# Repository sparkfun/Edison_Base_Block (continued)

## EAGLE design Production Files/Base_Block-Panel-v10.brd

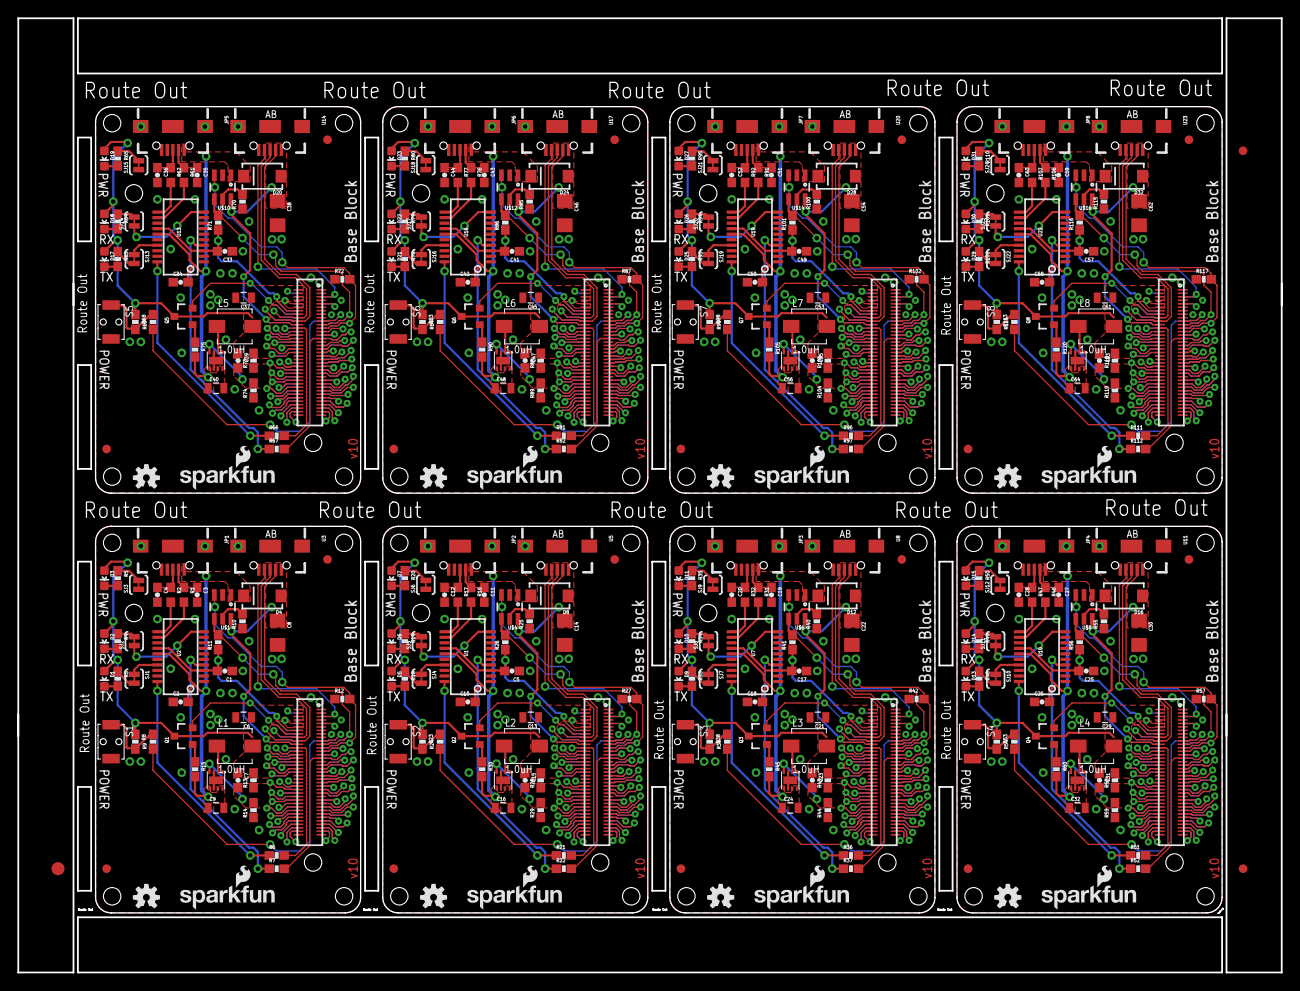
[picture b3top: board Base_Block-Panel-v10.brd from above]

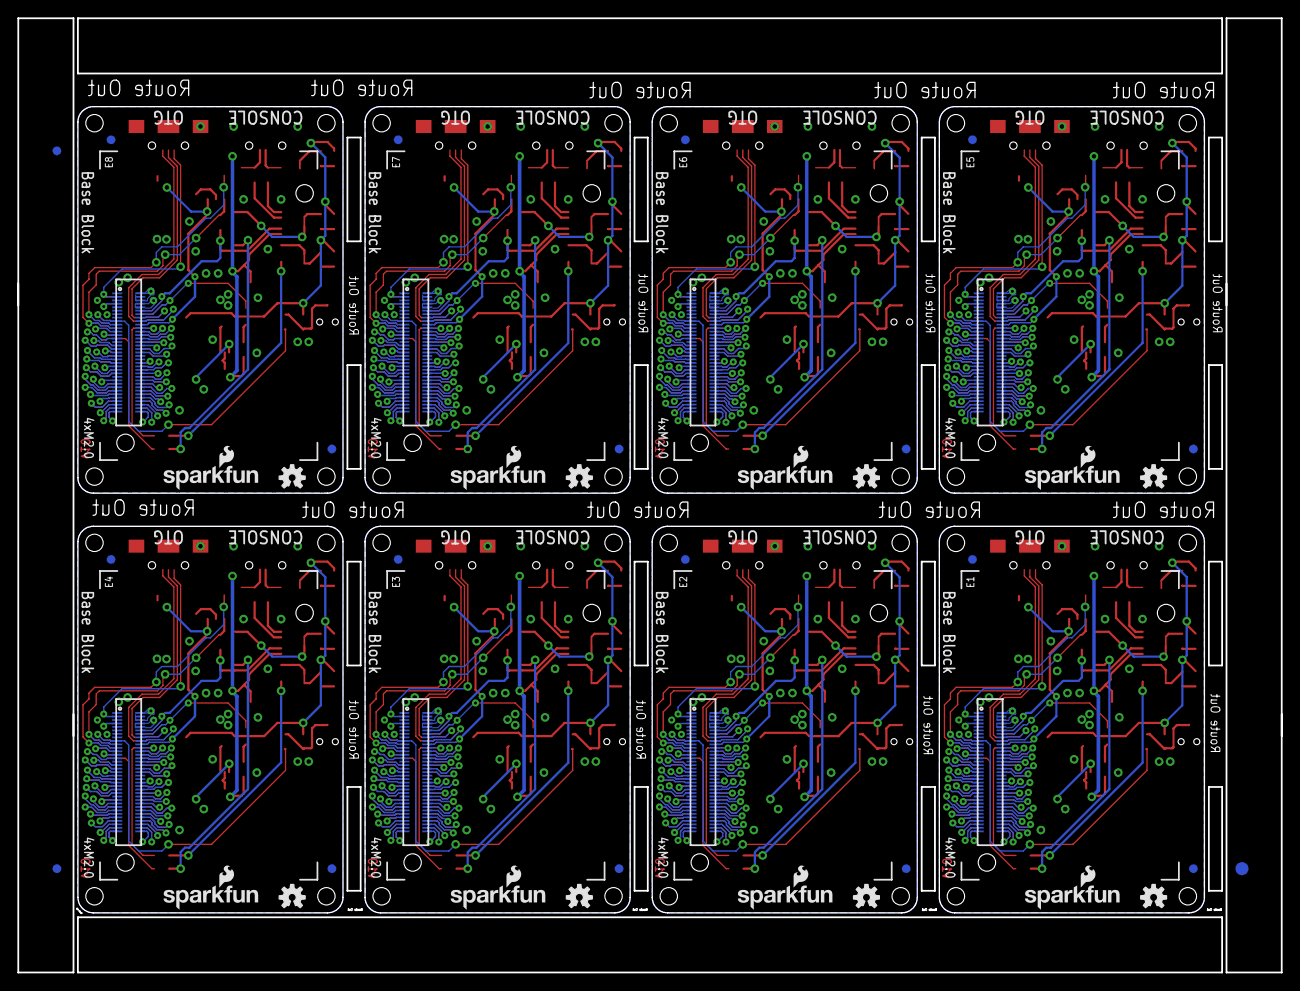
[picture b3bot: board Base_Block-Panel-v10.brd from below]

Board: 2 copper layers, 145.3 x 109.7 mm, 390 parts (51 on the bottom side), 624 nets.

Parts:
C1, C2, C5, C10, C17, C18, C25, C26, C33, C34, C41, C42, C49, C50, C57, C58: 0.1uF; 0603-CAP
C3, C4, C7, C11, C12, C15, C19, C20, C23, C27, C28, C31, C35, C36, C39, C43, C44, C47, C51, C52, C55, C59, C60, C63: 47pF; 0603-CAP
C6, C9, C13, C16, C21, C24, C29, C32, C37, C40, C45, C48, C53, C56, C61, C64: 22uF; 0805
C8, C14, C22, C30, C38, C46, C54, C62: 10uF; 1206
D1, D5, D9, D13, D17, D21, D25, D29: RED; LED-0603
D2, D6, D10, D14, D18, D22, D26, D30: YELLOW; LED-0603
D3, D7, D11, D15, D19, D23, D27, D31: BLUE; LED-0603
D4, D8, D12, D16, D20, D24, D28, D32: SMA-DIODE
E1, E2, E3, E4, E5, E6, E7, E8: EDISON_CONNECTOR_FULLMOUNTING_HOLES; EDISON_DAUGHTER
E$1, E$2: FIDUCIAL-1.5X3
E$3, E$4, E$5, E$6: FIDUCIAL-1X2
FID1, FID2, FID3, FID4, FID5, FID6, FID7, FID8, FID9, FID10, FID11, FID12, FID13, FID14, FID15, FID16, FID17, FID18, FID19, FID20, FID21, FID22, FID23, FID24, FID25, FID26, FID27, FID28, FID29, FID30, FID31, FID32: FIDUCIAL1X2; FIDUCIAL-1X2
JP1, JP2, JP3, JP4, JP5, JP6, JP7, JP8: USB_MICROB; USB-B-MICRO-SMD_V03
L1, L2, L3, L4, L5, L6, L7, L8: 1.0uH; INDUCTOR-SRP4020
LOGO1, LOGO3, LOGO6, LOGO7, LOGO10, LOGO11, LOGO14, LOGO15, LOGO18, LOGO19, LOGO22, LOGO23, LOGO26, LOGO27, LOGO30, LOGO31: SFE_LOGO_NAME_FLAME.1_INCH; SFE_LOGO_NAME_FLAME_.1
LOGO2, LOGO4, LOGO5, LOGO8, LOGO9, LOGO12, LOGO13, LOGO16, LOGO17, LOGO20, LOGO21, LOGO24, LOGO25, LOGO28, LOGO29, LOGO32: OSHW-LOGOS; OSHW-LOGO-S
Q1, Q2, Q3, Q4, Q5, Q6, Q7, Q8: BSS138; SOT23-3
R1, R2, R16, R17, R31, R32, R46, R47, R61, R62, R76, R77, R91, R92, R106, R107: 27; 0603
R3, R4, R5, R15, R18, R19, R20, R30, R33, R34, R35, R45, R48, R49, R50, R60, R63, R64, R65, R75, R78, R79, R80, R90, R93, R94, R95, R105, R108, R109, R110, R120: 1K; 0603-RES
R6, R7, R21, R22, R36, R37, R51, R52, R66, R67, R81, R82, R96, R97, R111, R112: 100; 0603-RES
R8, R11, R23, R26, R38, R41, R53, R56, R68, R71, R83, R86, R98, R101, R113, R116: 10K; 0603-RES
R9, R24, R39, R54, R69, R84, R99, R114: 220; 0603-RES
R10, R25, R40, R55, R70, R85, R100, R115: 287; 0603-RES
R12, R27, R42, R57, R72, R87, R102, R117: 100k; 0603-RES
R13, R28, R43, R58, R73, R88, R103, R118: 680k; 0603-RES
R14, R29, R44, R59, R74, R89, R104, R119: 120k; 0603-RES
S1, S2, S3, S4, S5, S6, S7, S8: POWER; TACTILE_SWITCH-SMD-RIGHT-ANGLE
SJ1, SJ2, SJ3, SJ4, SJ5, SJ6, SJ7, SJ8, SJ9, SJ10, SJ11, SJ12, SJ13, SJ14, SJ15, SJ16, SJ17, SJ18, SJ19, SJ20, SJ21, SJ22, SJ23, SJ24: JUMPER-PAD-2-NC_BY_TRACE; PAD-JUMPER-2-NC_BY_TRACE_YES_SILK
U1, U2, U7, U10, U13, U16, U19, U22: FTS31XS-U; SSOP20_L
U3, U5, U8, U11, U14, U17, U20, U23: USB-AB-MICRO-SMD_V03
U4, U6, U9, U12, U15, U18, U21, U24: TPS62065; WSON-8-PAD
U$1, U$4, U$6, U$8, U$10, U$12, U$14, U$16: MIC2039; SOT23-6
U$2, U$3, U$5, U$7, U$9, U$11, U$13, U$15: EDISON_CONNECTOR_FULLHEADER; DF40C-70DP-0.4(51)

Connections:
1.8V: C1.2, E1.12, R11.1, U2.3, U2.14, U$3.12
1.8V1: C5.2, E2.12, R26.1, U1.3, U1.14, U$2.12
1.8V2: C17.2, E3.12, R41.1, U7.3, U7.14, U$5.12
1.8V3: C25.2, E4.12, R56.1, U10.3, U10.14, U$7.12
1.8V4: C33.2, E5.12, R71.1, U13.3, U13.14, U$9.12
1.8V5: C41.2, E6.12, R86.1, U16.3, U16.14, U$11.12
1.8V6: C49.2, E7.12, R101.1, U19.3, U19.14, U$13.12
1.8V7: C57.2, E8.12, R116.1, U22.3, U22.14, U$15.12
3.3V: E1.8, E1.10, U$3.8, U$3.10
3.3V1: E2.8, E2.10, U$2.8, U$2.10
3.3V2: E3.8, E3.10, U$5.8, U$5.10
3.3V3: E4.8, E4.10, U$7.8, U$7.10
3.3V4: E5.8, E5.10, U$9.8, U$9.10
3.3V5: E6.8, E6.10, U$11.8, U$11.10
3.3V6: E7.8, E7.10, U$13.8, U$13.10
3.3V7: E8.8, E8.10, U$15.8, U$15.10
5V: C2.2, C9.1, D4.C, JP1.VBUS1, R15.2, U2.15, U4.5, U4.7, U4.8, U$1.1
5V1: C10.2, C16.1, D8.C, JP2.VBUS1, R30.2, U1.15, U6.5, U6.7, U6.8, U$4.1
5V2: C18.2, C24.1, D12.C, JP3.VBUS1, R45.2, U7.15, U9.5, U9.7, U9.8, U$6.1
5V3: C26.2, C32.1, D16.C, JP4.VBUS1, R60.2, U10.15, U12.5, U12.7, U12.8, U$8.1
5V4: C34.2, C40.1, D20.C, JP5.VBUS1, R75.2, U13.15, U15.5, U15.7, U15.8, U$10.1
5V5: C42.2, C48.1, D24.C, JP6.VBUS1, R90.2, U16.15, U18.5, U18.7, U18.8, U$12.1
5V6: C50.2, C56.1, D28.C, JP7.VBUS1, R105.2, U19.15, U21.5, U21.7, U21.8, U$14.1
5V7: C58.2, C64.1, D32.C, JP8.VBUS1, R120.2, U22.15, U24.5, U24.7, U24.8, U$16.1
DCIN: E1.14, Q1.2, U$3.14
DCIN1: E2.14, Q2.2, U$2.14
DCIN2: E3.14, Q3.2, U$5.14
DCIN3: E4.14, Q4.2, U$7.14
DCIN4: E5.14, Q5.2, U$9.14
DCIN5: E6.14, Q6.2, U$11.14
DCIN6: E7.14, Q7.2, U$13.14
DCIN7: E8.14, Q8.2, U$15.14
FAULT: E1.19, R11.2, U$1.4, U$3.19
FAULT1: E2.19, R26.2, U$2.19, U$4.4
FAULT2: E3.19, R41.2, U$5.19, U$6.4
FAULT3: E4.19, R56.2, U$7.19, U$8.4
FAULT4: E5.19, R71.2, U$9.19, U$10.4
FAULT5: E6.19, R86.2, U$11.19, U$12.4
FAULT6: E7.19, R101.2, U$13.19, U$14.4
FAULT7: E8.19, R116.2, U$15.19, U$16.4
FW_RCVR: E1.69, U$3.69
FW_RCVR1: E2.69, U$2.69
FW_RCVR2: E3.69, U$5.69
FW_RCVR3: E4.69, U$7.69
FW_RCVR4: E5.69, U$9.69
FW_RCVR5: E6.69, U$11.69
FW_RCVR6: E7.69, U$13.69
FW_RCVR7: E8.69, U$15.69
GND: C1.1, C2.1, C3.2, C4.2, C6.2, C8.2, C9.2, E1.1, E1.5, E1.9, E1.11, E1.13, E1.15, JP1.GND1, JP1.SHIELD1, JP1.SHIELD2, JP1.SHIELD3, R10.1, R12.1, R14.1, S1.2, SJ3.1, U2.6, U2.16, U3.GND1, U4.1, U4.3, U4.6, U4.PAD, U$1.2, U$3.1, U$3.5, U$3.9, U$3.11, U$3.13, U$3.15
GND1: C5.1, C10.1, C11.2, C12.2, C13.2, C14.2, C16.2, E2.1, E2.5, E2.9, E2.11, E2.13, E2.15, JP2.GND1, JP2.SHIELD1, JP2.SHIELD2, JP2.SHIELD3, R25.1, R27.1, R29.1, S2.2, SJ6.1, U1.6, U1.16, U5.GND1, U6.1, U6.3, U6.6, U6.PAD, U$2.1, U$2.5, U$2.9, U$2.11, U$2.13, U$2.15, U$4.2
GND2: C17.1, C18.1, C19.2, C20.2, C21.2, C22.2, C24.2, E3.1, E3.5, E3.9, E3.11, E3.13, E3.15, JP3.GND1, JP3.SHIELD1, JP3.SHIELD2, JP3.SHIELD3, R40.1, R42.1, R44.1, S3.2, SJ9.1, U7.6, U7.16, U8.GND1, U9.1, U9.3, U9.6, U9.PAD, U$5.1, U$5.5, U$5.9, U$5.11, U$5.13, U$5.15, U$6.2
GND3: C25.1, C26.1, C27.2, C28.2, C29.2, C30.2, C32.2, E4.1, E4.5, E4.9, E4.11, E4.13, E4.15, JP4.GND1, JP4.SHIELD1, JP4.SHIELD2, JP4.SHIELD3, R55.1, R57.1, R59.1, S4.2, SJ12.1, U10.6, U10.16, U11.GND1, U12.1, U12.3, U12.6, U12.PAD, U$7.1, U$7.5, U$7.9, U$7.11, U$7.13, U$7.15, U$8.2
GND4: C33.1, C34.1, C35.2, C36.2, C37.2, C38.2, C40.2, E5.1, E5.5, E5.9, E5.11, E5.13, E5.15, JP5.GND1, JP5.SHIELD1, JP5.SHIELD2, JP5.SHIELD3, R70.1, R72.1, R74.1, S5.2, SJ15.1, U13.6, U13.16, U14.GND1, U15.1, U15.3, U15.6, U15.PAD, U$9.1, U$9.5, U$9.9, U$9.11, U$9.13, U$9.15, U$10.2
GND5: C41.1, C42.1, C43.2, C44.2, C45.2, C46.2, C48.2, E6.1, E6.5, E6.9, E6.11, E6.13, E6.15, JP6.GND1, JP6.SHIELD1, JP6.SHIELD2, JP6.SHIELD3, R85.1, R87.1, R89.1, S6.2, SJ18.1, U16.6, U16.16, U17.GND1, U18.1, U18.3, U18.6, U18.PAD, U$11.1, U$11.5, U$11.9, U$11.11, U$11.13, U$11.15, U$12.2
GND6: C49.1, C50.1, C51.2, C52.2, C53.2, C54.2, C56.2, E7.1, E7.5, E7.9, E7.11, E7.13, E7.15, JP7.GND1, JP7.SHIELD1, JP7.SHIELD2, JP7.SHIELD3, R100.1, R102.1, R104.1, S7.2, SJ21.1, U19.6, U19.16, U20.GND1, U21.1, U21.3, U21.6, U21.PAD, U$13.1, U$13.5, U$13.9, U$13.11, U$13.13, U$13.15, U$14.2
GND7: C57.1, C58.1, C59.2, C60.2, C61.2, C62.2, C64.2, E8.1, E8.5, E8.9, E8.11, E8.13, E8.15, JP8.GND1, JP8.SHIELD1, JP8.SHIELD2, JP8.SHIELD3, R115.1, R117.1, R119.1, S8.2, SJ24.1, U22.6, U22.16, U23.GND1, U24.1, U24.3, U24.6, U24.PAD, U$15.1, U$15.5, U$15.9, U$15.11, U$15.13, U$15.15, U$16.2
GP1: E2.48, U$2.48
GP2: E2.42, U$2.42
GP3: E2.34, U$2.34
GP4: E2.32, U$2.32
GP5: E2.30, U$2.30
GP6: E2.28, U$2.28
GP7: E2.26, U$2.26
GP8: E2.25, U$2.25
GP9: E2.24, U$2.24
GP10: E3.48, U$5.48
GP11: E3.42, U$5.42
GP12: E3.34, U$5.34
GP12_PWM0: E1.35, U$3.35
GP12_PWM1: E2.35, U$2.35
GP12_PWM2: E3.35, U$5.35
GP12_PWM3: E4.35, U$7.35
GP12_PWM4: E5.35, U$9.35
GP12_PWM5: E6.35, U$11.35
GP12_PWM6: E7.35, U$13.35
GP12_PWM7: E8.35, U$15.35
GP13: E3.32, U$5.32
GP13_PWM1: E1.33, U$3.33
GP13_PWM2: E2.33, U$2.33
GP13_PWM3: E3.33, U$5.33
GP13_PWM4: E4.33, U$7.33
GP13_PWM5: E5.33, U$9.33
GP13_PWM6: E6.33, U$11.33
GP13_PWM7: E7.33, U$13.33
GP13_PWM8: E8.33, U$15.33
GP14: E1.48, U$3.48
GP15: E1.42, U$3.42
GP16: E3.30, U$5.30
GP17: E3.28, U$5.28
GP18: E3.26, U$5.26
GP19: E3.25, U$5.25
GP19_I2C_1_SCL: E1.41, U$3.41
GP19_I2C_1_SCL1: E2.41, U$2.41
GP19_I2C_1_SCL2: E3.41, U$5.41
GP19_I2C_1_SCL3: E4.41, U$7.41
GP19_I2C_1_SCL4: E5.41, U$9.41
GP19_I2C_1_SCL5: E6.41, U$11.41
GP19_I2C_1_SCL6: E7.41, U$13.41
GP19_I2C_1_SCL7: E8.41, U$15.41
GP20: E3.24, U$5.24
GP20_I2C_1_SDA: E1.43, U$3.43
GP20_I2C_1_SDA1: E2.43, U$2.43
GP20_I2C_1_SDA2: E3.43, U$5.43
GP20_I2C_1_SDA3: E4.43, U$7.43
GP20_I2C_1_SDA4: E5.43, U$9.43
GP20_I2C_1_SDA5: E6.43, U$11.43
GP20_I2C_1_SDA6: E7.43, U$13.43
GP20_I2C_1_SDA7: E8.43, U$15.43
GP21: E4.48, U$7.48
GP22: E4.42, U$7.42
GP23: E4.34, U$7.34
GP24: E4.32, U$7.32
GP25: E4.30, U$7.30
GP26: E4.28, U$7.28
GP27: E4.26, U$7.26
GP27_I2C_6_SCL: E1.45, U$3.45
GP27_I2C_6_SCL1: E2.45, U$2.45
GP27_I2C_6_SCL2: E3.45, U$5.45
GP27_I2C_6_SCL3: E4.45, U$7.45
GP27_I2C_6_SCL4: E5.45, U$9.45
GP27_I2C_6_SCL5: E6.45, U$11.45
GP27_I2C_6_SCL6: E7.45, U$13.45
GP27_I2C_6_SCL7: E8.45, U$15.45
GP28: E4.25, U$7.25
GP28_I2C_6_SDA: E1.47, U$3.47
GP28_I2C_6_SDA1: E2.47, U$2.47
GP28_I2C_6_SDA2: E3.47, U$5.47
GP28_I2C_6_SDA3: E4.47, U$7.47
GP28_I2C_6_SDA4: E5.47, U$9.47
GP28_I2C_6_SDA5: E6.47, U$11.47
GP28_I2C_6_SDA6: E7.47, U$13.47
GP28_I2C_6_SDA7: E8.47, U$15.47
GP29: E4.24, U$7.24
GP30: E5.48, U$9.48
GP31: E5.42, U$9.42
GP32: E5.34, U$9.34
GP33: E5.32, U$9.32
GP34: E5.30, U$9.30
GP35: E5.28, U$9.28
GP36: E5.26, U$9.26
GP37: E5.25, U$9.25
GP38: E5.24, U$9.24
GP39: E6.48, U$11.48
GP40: E6.42, U$11.42
GP40_I2S_2_CLK: E1.52, U$3.52
GP40_I2S_2_CLK1: E2.52, U$2.52
GP40_I2S_2_CLK2: E3.52, U$5.52
GP40_I2S_2_CLK3: E4.52, U$7.52
GP40_I2S_2_CLK4: E5.52, U$9.52
GP40_I2S_2_CLK5: E6.52, U$11.52
GP40_I2S_2_CLK6: E7.52, U$13.52
GP40_I2S_2_CLK7: E8.52, U$15.52
GP41: E6.34, U$11.34
GP41_I2S_2_FS: E1.54, U$3.54
GP41_I2S_2_FS1: E2.54, U$2.54
GP41_I2S_2_FS2: E3.54, U$5.54
GP41_I2S_2_FS3: E4.54, U$7.54
GP41_I2S_2_FS4: E5.54, U$9.54
GP41_I2S_2_FS5: E6.54, U$11.54
GP41_I2S_2_FS6: E7.54, U$13.54
GP41_I2S_2_FS7: E8.54, U$15.54
GP42: E6.32, U$11.32
GP42_I2S_2_RXD: E1.50, U$3.50
GP42_I2S_2_RXD1: E2.50, U$2.50
GP42_I2S_2_RXD2: E3.50, U$5.50
GP42_I2S_2_RXD3: E4.50, U$7.50
GP42_I2S_2_RXD4: E5.50, U$9.50
GP42_I2S_2_RXD5: E6.50, U$11.50
GP42_I2S_2_RXD6: E7.50, U$13.50
GP42_I2S_2_RXD7: E8.50, U$15.50
GP43: E6.30, U$11.30
GP43_I2S_2_TXD: E1.56, U$3.56
GP43_I2S_2_TXD1: E2.56, U$2.56
GP43_I2S_2_TXD2: E3.56, U$5.56
GP43_I2S_2_TXD3: E4.56, U$7.56
GP43_I2S_2_TXD4: E5.56, U$9.56
GP43_I2S_2_TXD5: E6.56, U$11.56
GP43_I2S_2_TXD6: E7.56, U$13.56
GP43_I2S_2_TXD7: E8.56, U$15.56
GP44: E1.24, U$3.24
GP45: E1.26, U$3.26
GP46: E1.28, U$3.28
GP47: E1.30, U$3.30
GP48: E1.32, U$3.32
GP49: E1.34, U$3.34
GP50: E6.28, U$11.28
GP51: E6.26, U$11.26
GP52: E6.25, U$11.25
GP53: E6.24, U$11.24
GP54: E7.48, U$13.48
GP55: E7.42, U$13.42
GP56: E7.34, U$13.34
GP57: E7.32, U$13.32
GP58: E7.30, U$13.30
GP59: E7.28, U$13.28
GP60: E7.26, U$13.26
GP61: E7.25, U$13.25
GP62: E7.24, U$13.24
GP63: E8.48, U$15.48
GP64: E8.42, U$15.42
GP65: E8.34, U$15.34
GP66: E8.32, U$15.32
GP67: E8.30, U$15.30
GP68: E8.28, U$15.28
GP69: E8.26, U$15.26
GP70: E8.25, U$15.25
GP71: E8.24, U$15.24
GP77_SD_0_CD#: E1.60, U$3.60
GP77_SD_0_CD#1: E2.60, U$2.60
GP77_SD_0_CD#2: E3.60, U$5.60
GP77_SD_0_CD#3: E4.60, U$7.60
GP77_SD_0_CD#4: E5.60, U$9.60
GP77_SD_0_CD#5: E6.60, U$11.60
GP77_SD_0_CD#6: E7.60, U$13.60
GP77_SD_0_CD#7: E8.60, U$15.60
GP78_SD_0_CLK: E1.58, U$3.58
GP78_SD_0_CLK1: E2.58, U$2.58
GP78_SD_0_CLK2: E3.58, U$5.58
GP78_SD_0_CLK3: E4.58, U$7.58
GP78_SD_0_CLK4: E5.58, U$9.58
GP78_SD_0_CLK5: E6.58, U$11.58
GP78_SD_0_CLK6: E7.58, U$13.58
GP78_SD_0_CLK7: E8.58, U$15.58
GP79_SD_0_CMD: E1.62, U$3.62
GP79_SD_0_CMD1: E2.62, U$2.62
GP79_SD_0_CMD2: E3.62, U$5.62
GP79_SD_0_CMD3: E4.62, U$7.62
GP79_SD_0_CMD4: E5.62, U$9.62
GP79_SD_0_CMD5: E6.62, U$11.62
GP79_SD_0_CMD6: E7.62, U$13.62
GP79_SD_0_CMD7: E8.62, U$15.62
GP80_SD_0_DAT0: E1.66, U$3.66
GP80_SD_0_DAT1: E2.66, U$2.66
GP80_SD_0_DAT2: E3.66, U$5.66
GP80_SD_0_DAT3: E4.66, U$7.66
GP80_SD_0_DAT4: E5.66, U$9.66
GP80_SD_0_DAT5: E6.66, U$11.66
GP80_SD_0_DAT6: E7.66, U$13.66
GP80_SD_0_DAT7: E8.66, U$15.66
GP81_SD_0_DAT1: E1.70, U$3.70
GP81_SD_0_DAT2: E2.70, U$2.70
GP81_SD_0_DAT3: E3.70, U$5.70
GP81_SD_0_DAT4: E4.70, U$7.70
GP81_SD_0_DAT5: E5.70, U$9.70
GP81_SD_0_DAT6: E6.70, U$11.70
GP81_SD_0_DAT7: E7.70, U$13.70
GP81_SD_0_DAT8: E8.70, U$15.70
GP82_SD_0_DAT1: E2.64, U$2.64
GP82_SD_0_DAT2: E1.64, U$3.64
GP82_SD_0_DAT3: E3.64, U$5.64
GP82_SD_0_DAT4: E4.64, U$7.64
GP82_SD_0_DAT5: E5.64, U$9.64
GP82_SD_0_DAT6: E6.64, U$11.64
GP82_SD_0_DAT7: E7.64, U$13.64
GP82_SD_0_DAT8: E8.64, U$15.64
GP83_SD_0_DAT1: E2.68, U$2.68
GP83_SD_0_DAT2: E3.68, U$5.68
GP83_SD_0_DAT3: E1.68, U$3.68
GP83_SD_0_DAT4: E4.68, U$7.68
GP83_SD_0_DAT5: E5.68, U$9.68
GP83_SD_0_DAT6: E6.68, U$11.68
GP83_SD_0_DAT7: E7.68, U$13.68
GP83_SD_0_DAT8: E8.68, U$15.68
GP84_SD_CLK_FB: E1.44, U$3.44
GP84_SD_CLK_FB1: E2.44, U$2.44
GP84_SD_CLK_FB2: E3.44, U$5.44
GP84_SD_CLK_FB3: E4.44, U$7.44
GP84_SD_CLK_FB4: E5.44, U$9.44
GP84_SD_CLK_FB5: E6.44, U$11.44
GP84_SD_CLK_FB6: E7.44, U$13.44
GP84_SD_CLK_FB7: E8.44, U$15.44
GP109_SPI_2_CLK: E1.55, U$3.55
GP109_SPI_2_CLK1: E2.55, U$2.55
GP109_SPI_2_CLK2: E3.55, U$5.55
GP109_SPI_2_CLK3: E4.55, U$7.55
GP109_SPI_2_CLK4: E5.55, U$9.55
GP109_SPI_2_CLK5: E6.55, U$11.55
GP109_SPI_2_CLK6: E7.55, U$13.55
GP109_SPI_2_CLK7: E8.55, U$15.55
GP110_SPI_2_FS0: E1.53, U$3.53
GP110_SPI_2_FS1: E2.53, U$2.53
GP110_SPI_2_FS2: E3.53, U$5.53
GP110_SPI_2_FS3: E4.53, U$7.53
GP110_SPI_2_FS4: E5.53, U$9.53
GP110_SPI_2_FS5: E6.53, U$11.53
GP110_SPI_2_FS6: E7.53, U$13.53
GP110_SPI_2_FS7: E8.53, U$15.53
GP111_SPI_2_FS1: E1.51, U$3.51
GP111_SPI_2_FS2: E2.51, U$2.51
GP111_SPI_2_FS3: E3.51, U$5.51
GP111_SPI_2_FS4: E4.51, U$7.51
GP111_SPI_2_FS5: E5.51, U$9.51
GP111_SPI_2_FS6: E6.51, U$11.51
GP111_SPI_2_FS7: E7.51, U$13.51
GP111_SPI_2_FS8: E8.51, U$15.51
GP114_SPI_2_RXD: E1.59, U$3.59
GP114_SPI_2_RXD1: E2.59, U$2.59
GP114_SPI_2_RXD2: E3.59, U$5.59
GP114_SPI_2_RXD3: E4.59, U$7.59
GP114_SPI_2_RXD4: E5.59, U$9.59
GP114_SPI_2_RXD5: E6.59, U$11.59
GP114_SPI_2_RXD6: E7.59, U$13.59
GP114_SPI_2_RXD7: E8.59, U$15.59
GP115_SPI_2_TXD: E1.57, U$3.57
GP115_SPI_2_TXD1: E2.57, U$2.57
GP115_SPI_2_TXD2: E3.57, U$5.57
GP115_SPI_2_TXD3: E4.57, U$7.57
GP115_SPI_2_TXD4: E5.57, U$9.57
GP115_SPI_2_TXD5: E6.57, U$11.57
GP115_SPI_2_TXD6: E7.57, U$13.57
GP115_SPI_2_TXD7: E8.57, U$15.57
GP128_UART_1_CTS: E1.65, U$3.65
GP128_UART_1_CTS1: E2.65, U$2.65
GP128_UART_1_CTS2: E3.65, U$5.65
GP128_UART_1_CTS3: E4.65, U$7.65
GP128_UART_1_CTS4: E5.65, U$9.65
GP128_UART_1_CTS5: E6.65, U$11.65
GP128_UART_1_CTS6: E7.65, U$13.65
GP128_UART_1_CTS7: E8.65, U$15.65
GP129_UART_1_RTS: E1.63, U$3.63
GP129_UART_1_RTS1: E2.63, U$2.63
GP129_UART_1_RTS2: E3.63, U$5.63
GP129_UART_1_RTS3: E4.63, U$7.63
GP129_UART_1_RTS4: E5.63, U$9.63
GP129_UART_1_RTS5: E6.63, U$11.63
GP129_UART_1_RTS6: E7.63, U$13.63
GP129_UART_1_RTS7: E8.63, U$15.63
GP130_UART_1_RX: E1.61, U$3.61
GP130_UART_1_RX1: E2.61, U$2.61
GP130_UART_1_RX2: E3.61, U$5.61
GP130_UART_1_RX3: E4.61, U$7.61
GP130_UART_1_RX4: E5.61, U$9.61
GP130_UART_1_RX5: E6.61, U$11.61
GP130_UART_1_RX6: E7.61, U$13.61
GP130_UART_1_RX7: E8.61, U$15.61
GP131_UART_1_TX: E1.46, U$3.46
GP131_UART_1_TX1: E2.46, U$2.46
GP131_UART_1_TX2: E3.46, U$5.46
GP131_UART_1_TX3: E4.46, U$7.46
GP131_UART_1_TX4: E5.46, U$9.46
GP131_UART_1_TX5: E6.46, U$11.46
GP131_UART_1_TX6: E7.46, U$13.46
GP131_UART_1_TX7: E8.46, U$15.46
GP134_UART_2_RX: E1.22, R6.2, U$3.22
GP134_UART_2_RX1: E2.22, R21.2, U$2.22
GP134_UART_2_RX2: E3.22, R36.2, U$5.22
GP134_UART_2_RX3: E4.22, R51.2, U$7.22
GP134_UART_2_RX4: E5.22, R66.2, U$9.22
GP134_UART_2_RX5: E6.22, R81.2, U$11.22
GP134_UART_2_RX6: E7.22, R96.2, U$13.22
GP134_UART_2_RX7: E8.22, R111.2, U$15.22
GP135_UART_2_TX: E1.27, R7.2, U$3.27
GP135_UART_2_TX1: E2.27, R22.2, U$2.27
GP135_UART_2_TX2: E3.27, R37.2, U$5.27
GP135_UART_2_TX3: E4.27, R52.2, U$7.27
GP135_UART_2_TX4: E5.27, R67.2, U$9.27
GP135_UART_2_TX5: E6.27, R82.2, U$11.27
GP135_UART_2_TX6: E7.27, R97.2, U$13.27
GP135_UART_2_TX7: E8.27, R112.2, U$15.27
GP165: E1.25, U$3.25
GP182_PWM1: E2.37, U$2.37
GP182_PWM2: E1.37, U$3.37
GP182_PWM3: E3.37, U$5.37
GP182_PWM4: E4.37, U$7.37
GP182_PWM5: E5.37, U$9.37
GP182_PWM6: E6.37, U$11.37
GP182_PWM7: E7.37, U$13.37
GP182_PWM8: E8.37, U$15.37
GP183_PWM1: E2.39, U$2.39
GP183_PWM2: E3.39, U$5.39
GP183_PWM3: E1.39, U$3.39
GP183_PWM4: E4.39, U$7.39
GP183_PWM5: E5.39, U$9.39
GP183_PWM6: E6.39, U$11.39
GP183_PWM7: E7.39, U$13.39
GP183_PWM8: E8.39, U$15.39
MSIC_SLP_CLK: E1.7, U$3.7
MSIC_SLP_CLK1: E2.7, U$2.7
MSIC_SLP_CLK2: E3.7, U$5.7
MSIC_SLP_CLK3: E4.7, U$7.7
MSIC_SLP_CLK4: E5.7, U$9.7
MSIC_SLP_CLK5: E6.7, U$11.7
MSIC_SLP_CLK6: E7.7, U$13.7
MSIC_SLP_CLK7: E8.7, U$15.7
unnamed: SJ1.1, U2.17
unnamed: C3.1, JP1.D-1, R1.1
unnamed: C4.1, JP1.D+1, R2.1
unnamed: R1.2, U2.12
unnamed: R2.2, U2.11
unnamed: SJ2.1, U2.10
unnamed: R3.1, SJ1.2
unnamed: R4.1, SJ2.2
unnamed: D1.C, R3.2
unnamed: D2.C, R4.2
unnamed: R6.1, U2.20
unnamed: D3.C, R5.2
unnamed: R5.1, SJ3.2
unnamed: R7.1, U2.4
unnamed: R8.2, R9.2, S1.1
unnamed: R10.2, U$1.5
unnamed: C7.2, R13.1, R14.2, U4.4
unnamed: Q1.1, R15.1
unnamed: L1.P$1, U4.2
unnamed: C11.1, JP2.D-1, R16.1
unnamed: C12.1, JP2.D+1, R17.1
unnamed: R16.2, U1.12
unnamed: R17.2, U1.11
unnamed: SJ4.1, U1.17
unnamed: SJ5.1, U1.10
unnamed: R18.1, SJ4.2
unnamed: R19.1, SJ5.2
unnamed: D5.C, R18.2
unnamed: D6.C, R19.2
unnamed: D7.C, R20.2
unnamed: R20.1, SJ6.2
unnamed: R21.1, U1.20
unnamed: R22.1, U1.4
unnamed: R23.2, R24.2, S2.1
unnamed: R25.2, U$4.5
unnamed: C15.2, R28.1, R29.2, U6.4
unnamed: L2.P$1, U6.2
unnamed: Q2.1, R30.1
unnamed: C19.1, JP3.D-1, R31.1
unnamed: C20.1, JP3.D+1, R32.1
unnamed: R31.2, U7.12
unnamed: R32.2, U7.11
unnamed: SJ7.1, U7.17
unnamed: SJ8.1, U7.10
unnamed: R33.1, SJ7.2
unnamed: R34.1, SJ8.2
unnamed: D9.C, R33.2
unnamed: D10.C, R34.2
unnamed: D11.C, R35.2
unnamed: R35.1, SJ9.2
unnamed: R36.1, U7.20
unnamed: R37.1, U7.4
unnamed: R38.2, R39.2, S3.1
unnamed: R40.2, U$6.5
unnamed: C23.2, R43.1, R44.2, U9.4
unnamed: L3.P$1, U9.2
unnamed: Q3.1, R45.1
unnamed: C27.1, JP4.D-1, R46.1
unnamed: C28.1, JP4.D+1, R47.1
unnamed: R46.2, U10.12
unnamed: R47.2, U10.11
unnamed: SJ10.1, U10.17
unnamed: SJ11.1, U10.10
unnamed: R48.1, SJ10.2
unnamed: R49.1, SJ11.2
unnamed: D13.C, R48.2
unnamed: D14.C, R49.2
unnamed: D15.C, R50.2
unnamed: R50.1, SJ12.2
unnamed: R51.1, U10.20
unnamed: R52.1, U10.4
unnamed: R53.2, R54.2, S4.1
unnamed: R55.2, U$8.5
unnamed: C31.2, R58.1, R59.2, U12.4
unnamed: L4.P$1, U12.2
unnamed: Q4.1, R60.1
unnamed: C35.1, JP5.D-1, R61.1
unnamed: C36.1, JP5.D+1, R62.1
unnamed: R61.2, U13.12
unnamed: R62.2, U13.11
unnamed: SJ13.1, U13.17
unnamed: SJ14.1, U13.10
unnamed: R63.1, SJ13.2
unnamed: R64.1, SJ14.2
unnamed: D17.C, R63.2
unnamed: D18.C, R64.2
unnamed: D19.C, R65.2
unnamed: R65.1, SJ15.2
unnamed: R66.1, U13.20
unnamed: R67.1, U13.4
unnamed: R68.2, R69.2, S5.1
unnamed: R70.2, U$10.5
unnamed: C39.2, R73.1, R74.2, U15.4
unnamed: L5.P$1, U15.2
unnamed: Q5.1, R75.1
unnamed: C43.1, JP6.D-1, R76.1
unnamed: C44.1, JP6.D+1, R77.1
unnamed: R76.2, U16.12
unnamed: R77.2, U16.11
unnamed: SJ16.1, U16.17
unnamed: SJ17.1, U16.10
unnamed: R78.1, SJ16.2
unnamed: R79.1, SJ17.2
unnamed: D21.C, R78.2
unnamed: D22.C, R79.2
unnamed: D23.C, R80.2
unnamed: R80.1, SJ18.2
unnamed: R81.1, U16.20
unnamed: R82.1, U16.4
unnamed: R83.2, R84.2, S6.1
unnamed: R85.2, U$12.5
unnamed: C47.2, R88.1, R89.2, U18.4
unnamed: L6.P$1, U18.2
unnamed: Q6.1, R90.1
unnamed: C51.1, JP7.D-1, R91.1
unnamed: C52.1, JP7.D+1, R92.1
unnamed: R91.2, U19.12
unnamed: R92.2, U19.11
unnamed: SJ19.1, U19.17
unnamed: SJ20.1, U19.10
unnamed: R93.1, SJ19.2
unnamed: R94.1, SJ20.2
unnamed: D25.C, R93.2
unnamed: D26.C, R94.2
unnamed: D27.C, R95.2
unnamed: R95.1, SJ21.2
unnamed: R96.1, U19.20
unnamed: R97.1, U19.4
unnamed: R98.2, R99.2, S7.1
unnamed: R100.2, U$14.5
unnamed: C55.2, R103.1, R104.2, U21.4
unnamed: L7.P$1, U21.2
unnamed: Q7.1, R105.1
unnamed: C59.1, JP8.D-1, R106.1
unnamed: C60.1, JP8.D+1, R107.1
unnamed: R106.2, U22.12
unnamed: R107.2, U22.11
unnamed: SJ22.1, U22.17
unnamed: SJ23.1, U22.10
unnamed: R108.1, SJ22.2
unnamed: R109.1, SJ23.2
unnamed: D29.C, R108.2
unnamed: D30.C, R109.2
unnamed: D31.C, R110.2
unnamed: R110.1, SJ24.2
unnamed: R111.1, U22.20
unnamed: R112.1, U22.4
unnamed: R113.2, R114.2, S8.1
unnamed: R115.2, U$16.5
unnamed: C63.2, R118.1, R119.2, U24.4
unnamed: L8.P$1, U24.2
unnamed: Q8.1, R120.1
OSC_CLK_OUT: E1.67, U$3.67
OSC_CLK_OUT1: E2.67, U$2.67
OSC_CLK_OUT2: E3.67, U$5.67
OSC_CLK_OUT3: E4.67, U$7.67
OSC_CLK_OUT4: E5.67, U$9.67
OSC_CLK_OUT5: E6.67, U$11.67
OSC_CLK_OUT6: E7.67, U$13.67
OSC_CLK_OUT7: E8.67, U$15.67
PSW: E1.21, R12.2, U$1.3, U$3.21
PSW1: E2.21, R27.2, U$2.21, U$4.3
PSW2: E3.21, R42.2, U$5.21, U$6.3
PSW3: E4.21, R57.2, U$7.21, U$8.3
PSW4: E5.21, R72.2, U$9.21, U$10.3
PSW5: E6.21, R87.2, U$11.21, U$12.3
PSW6: E7.21, R102.2, U$13.21, U$14.3
PSW7: E8.21, R117.2, U$15.21, U$16.3
PWRBTN#: E1.17, R9.1, U$3.17
PWRBTN#1: E2.17, R24.1, U$2.17
PWRBTN#2: E3.17, R39.1, U$5.17
PWRBTN#3: E4.17, R54.1, U$7.17
PWRBTN#4: E5.17, R69.1, U$9.17
PWRBTN#5: E6.17, R84.1, U$11.17
PWRBTN#6: E7.17, R99.1, U$13.17
PWRBTN#7: E8.17, R114.1, U$15.17
RCVR_MODE: E1.31, U$3.31
RCVR_MODE1: E2.31, U$2.31
RCVR_MODE2: E3.31, U$5.31
RCVR_MODE3: E4.31, U$7.31
RCVR_MODE4: E5.31, U$9.31
RCVR_MODE5: E6.31, U$11.31
RCVR_MODE6: E7.31, U$13.31
RCVR_MODE7: E8.31, U$15.31
RESET_OUT#: E1.36, U$3.36
RESET_OUT#1: E2.36, U$2.36
RESET_OUT#2: E3.36, U$5.36
RESET_OUT#3: E4.36, U$7.36
RESET_OUT#4: E5.36, U$9.36
RESET_OUT#5: E6.36, U$11.36
RESET_OUT#6: E7.36, U$13.36
RESET_OUT#7: E8.36, U$15.36
USB_DN: E1.18, U3.D-1, U$3.18
USB_DN1: E2.18, U5.D-1, U$2.18
USB_DN2: E3.18, U8.D-1, U$5.18
USB_DN3: E4.18, U11.D-1, U$7.18
USB_DN4: E5.18, U14.D-1, U$9.18
USB_DN5: E6.18, U17.D-1, U$11.18
USB_DN6: E7.18, U20.D-1, U$13.18
USB_DN7: E8.18, U23.D-1, U$15.18
USB_DP: E1.16, U3.D+1, U$3.16
USB_DP1: E2.16, U5.D+1, U$2.16
USB_DP2: E3.16, U8.D+1, U$5.16
USB_DP3: E4.16, U11.D+1, U$7.16
USB_DP4: E5.16, U14.D+1, U$9.16
USB_DP5: E6.16, U17.D+1, U$11.16
USB_DP6: E7.16, U20.D+1, U$13.16
USB_DP7: E8.16, U23.D+1, U$15.16
USB_ID: E1.3, U3.ID1, U$3.3
USB_ID1: E2.3, U5.ID1, U$2.3
USB_ID2: E3.3, U8.ID1, U$5.3
USB_ID3: E4.3, U11.ID1, U$7.3
USB_ID4: E5.3, U14.ID1, U$9.3
USB_ID5: E6.3, U17.ID1, U$11.3
USB_ID6: E7.3, U20.ID1, U$13.3
USB_ID7: E8.3, U23.ID1, U$15.3
USB_VBUS: C8.1, D4.A, E1.20, U3.VBUS1, U$1.6, U$3.20
USB_VBUS1: C14.1, D8.A, E2.20, U5.VBUS1, U$2.20, U$4.6
USB_VBUS2: C22.1, D12.A, E3.20, U8.VBUS1, U$5.20, U$6.6
USB_VBUS3: C30.1, D16.A, E4.20, U11.VBUS1, U$7.20, U$8.6
USB_VBUS4: C38.1, D20.A, E5.20, U14.VBUS1, U$9.20, U$10.6
USB_VBUS5: C46.1, D24.A, E6.20, U17.VBUS1, U$11.20, U$12.6
USB_VBUS6: C54.1, D28.A, E7.20, U20.VBUS1, U$13.20, U$14.6
USB_VBUS7: C62.1, D32.A, E8.20, U23.VBUS1, U$15.20, U$16.6
VSYS: C6.1, C7.1, D1.A, D2.A, D3.A, E1.2, E1.4, E1.6, L1.P$2, Q1.3, R8.1, R13.2, U$3.2, U$3.4, U$3.6
VSYS1: C13.1, C15.1, D5.A, D6.A, D7.A, E2.2, E2.4, E2.6, L2.P$2, Q2.3, R23.1, R28.2, U$2.2, U$2.4, U$2.6
VSYS2: C21.1, C23.1, D9.A, D10.A, D11.A, E3.2, E3.4, E3.6, L3.P$2, Q3.3, R38.1, R43.2, U$5.2, U$5.4, U$5.6
VSYS3: C29.1, C31.1, D13.A, D14.A, D15.A, E4.2, E4.4, E4.6, L4.P$2, Q4.3, R53.1, R58.2, U$7.2, U$7.4, U$7.6
VSYS4: C37.1, C39.1, D17.A, D18.A, D19.A, E5.2, E5.4, E5.6, L5.P$2, Q5.3, R68.1, R73.2, U$9.2, U$9.4, U$9.6
VSYS5: C45.1, C47.1, D21.A, D22.A, D23.A, E6.2, E6.4, E6.6, L6.P$2, Q6.3, R83.1, R88.2, U$11.2, U$11.4, U$11.6
VSYS6: C53.1, C55.1, D25.A, D26.A, D27.A, E7.2, E7.4, E7.6, L7.P$2, Q7.3, R98.1, R103.2, U$13.2, U$13.4, U$13.6
VSYS7: C61.1, C63.1, D29.A, D30.A, D31.A, E8.2, E8.4, E8.6, L8.P$2, Q8.3, R113.1, R118.2, U$15.2, U$15.4, U$15.6
V_BAT_BKUP: E1.23, U$3.23
V_BAT_BKUP1: E2.23, U$2.23
V_BAT_BKUP2: E3.23, U$5.23
V_BAT_BKUP3: E4.23, U$7.23
V_BAT_BKUP4: E5.23, U$9.23
V_BAT_BKUP5: E6.23, U$11.23
V_BAT_BKUP6: E7.23, U$13.23
V_BAT_BKUP7: E8.23, U$15.23
